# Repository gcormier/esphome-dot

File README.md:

# esphome-dot

Beginnings of a replacement PCB for Amazon Echo Dot v5.

# todo
- [x] Physical board dimensions
- [ ] Figure out pinout of ribbon cable
- [ ] figure out PDN mystery. it needs to be controlled to use register 0x00 for pullup settings
- [ ] Determine if ESP32 module can be used or needs custom design for RF purposes
- [ ] Schematic
- [ ] PCB design and layout
- [ ] BOM
- [ ] Firmware
- [ ] Manufacture

## dfm
- [ ] Holes around spring fingers for protective cap (1.6mm hole, 1.5mm plastic pin)

## Notice
Amazon Echo Dot is a trademark of Amazon.com, Inc. This project is not affiliated with Amazon.com, Inc. in any way.

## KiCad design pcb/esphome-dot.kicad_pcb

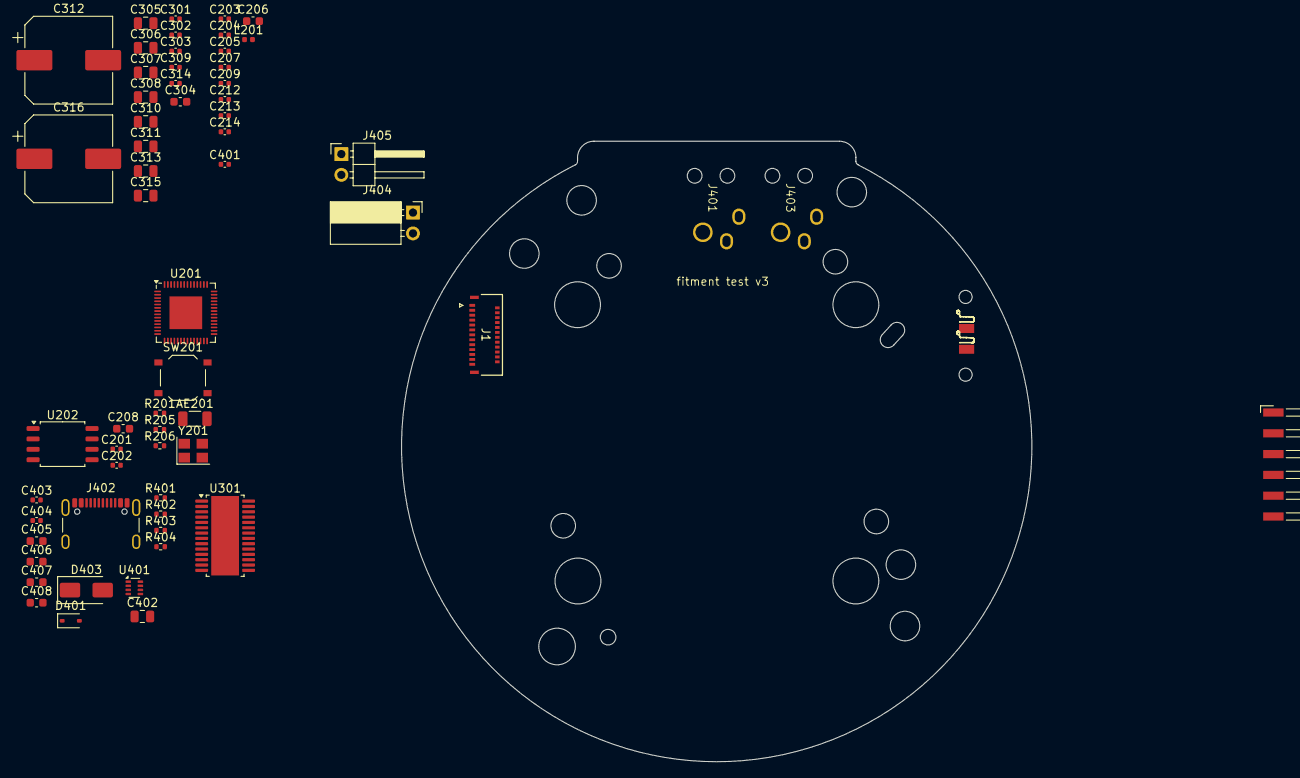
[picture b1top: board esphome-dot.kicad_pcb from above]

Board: 4 copper layers, 77.0 x 75.8 mm, 62 parts (0 on the bottom side), 44 nets, no tracks yet.

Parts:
AE201: ANT3216LL00R2400A; C_1206_3216Metric
C201, C202: 20pF; C_0402_1005Metric
C203, C205, C207, C209, C212, C213, C214, C303, C309, C314, C401, C403, C404: 100n; C_0402_1005Metric
C204, C301, C302: 1u; C_0402_1005Metric
C206, C208, C304, C405, C407, C408: 10u; C_0603_1608Metric
C305, C306, C307, C308: 220n; C_0805_2012Metric
C310, C315: 22u; C_0805_2012Metric
C311, C313: 680n; C_0805_2012Metric
C312, C316: 330u; CP_Elec_10x10.5
C402: 10u; C_0805_2012Metric
C406: 27p; C_0603_1608Metric
D401: CUS05S40.H3F; D_SOD-323
D403: SMAJ22A; D_SMA
J1: Input; CONN_502598-2593_MOLEX
J5: SPK1; SF2212
J6: SPK2; SF2212
J201: eflashy32; Harwin_M20-89006xx_1x06_P2.54mm_Horizontal
J401, J403: ADC-055B-9; BarrelJack_AdamTech_ADC-055B-9
J402: USBC; USB_C_Receptacle_GCT_USB4105-xx-A_16P_TopMnt_Horizontal
J404: 20V; PinSocket_1x02_P2.54mm_Horizontal
J405: 20v; PinHeader_1x02_P2.54mm_Horizontal
L201: 2nH; L_0402_1005Metric
R201: 22; R_0402_1005Metric
R205, R206: 10k; R_0402_1005Metric
R401, R402: 5k1; R_0402_1005Metric
R403: 68k; R_0402_1005Metric
R404: 22k; R_0402_1005Metric
SW201: RESET; SW_Push_1P1T_XKB_TS-1187A
U201: ESP32-S3R8; QFN-56-1EP_7x7mm_P0.4mm_EP4x4mm
U202: W25Q128JVSIQ; SOIC-8_5.23x5.23mm_P1.27mm
U301: TAS5805M; TSSOP-28-1EP_4.4x9.7mm_P0.65mm_EP3.4x9.7mm_Mask3.1x4.05mm
U401: TPS62932; SOT-583-8
Y201: 40MHz; Crystal_SMD_3225-4Pin_3.2x2.5mm

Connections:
3V3: C203.2, C204.2, C205.2, C206.2, C212.2, C213.2, C214.2, L201.1, U201.20 (VDD3P3_RTC), U201.46 (VDD3P3_CPU), U201.55 (VDDA), U201.56 (VDDA)
3V3_RF: C209.2, L201.2, U201.2 (VDD3P3), U201.3 (VDD3P3)
+3V3: C303.1, C304.1, C405.1, C406.1, C407.1, C408.1, J201.4, R205.1, R206.1, R403.2, U301.2 (DVDD)
+20V: C309.2, C310.2, C312.2, C314.2, C315.2, C316.2, C402.1, C403.2, D401.1 (K), D403.1 (K), J403.1, J405.1, U301.15 (PVDD), U301.16 (PVDD), U301.27 (PVDD), U301.28 (PVDD), U401.3 (VIN)
/MCU/EN: C208.2, J201.5, R205.2, U201.4 (CHIP_PU)
/MCU/GPIO0: J201.6, R206.2, SW201.1 (A), U201.5 (GPIO0)
/MCU/PROGRXD: J201.3, U201.50 (U0RXD)
/MCU/PROGTXD: J201.2, U201.49 (U0TXD)
/MCU/XTAL_N: C202.2, U201.53 (XTAL_N), Y201.3
/MCU/XTAL_P: R201.1, U201.54 (XTAL_P)
/Power/BST: C404.2, U401.6 (BST)
/Power/FB: C406.2, R403.1, R404.1, U401.8 (FB)
/Power/SW: C404.1, U401.5 (SW)
ADR: U201.41 (GPIO36), U301.3 (ADR)
GND: C201.1, C202.1, C203.1, C204.1, C205.1, C206.1, C207.2, C208.1, C209.1, C212.1, C213.1, C214.1, C301.1, C302.1, C303.2, C304.2, C309.1, C310.1, C311.1, C312.1, C313.1, C314.1, C315.1, C316.1, C401.1, C402.2, C403.1, C405.2, C407.2, C408.2, D403.2 (A), J201.1, J401.2, J402.A1 (GND), J402.A12 (GND), J402.B1 (GND), J402.B12 (GND), J403.2, J404.2, J405.2, R401.2, R402.2, R404.2, SW201.2 (B), U201.57 (GND), U202.4 (GND), U301.1 (DGND), U301.5 (DGND), U301.14 (AGND), U301.19 (PGND), U301.24 (PGND), U301.29 (EP), U401.1 (RT), U401.4 (GND), Y201.2, Y201.4
I2C_SDA: U201.18 (GPIO13), U301.10 (SDA)
I2C_SDL: U201.17 (GPIO12), U301.11 (SCL)
I2S1_CLK: U201.10 (GPIO5), U301.7 (SCLK)
I2S1_FSYNC: U201.9 (GPIO4), U301.6 (LRCLK)
I2S1_SD: U201.11 (GPIO6), U301.8 (SDIN)
unnamed: C201.2, R201.2, Y201.1
unnamed: D401.2 (A), J402.A4 (VBUS), J402.A9 (VBUS), J402.B4 (VBUS), J402.B9 (VBUS)
unnamed: J402.A5 (CC1), R402.1
unnamed: J402.B5 (CC2), R401.1
unnamed: J401.1, J404.1
unnamed: C302.2, U301.13 (AVDD)
unnamed: C305.1, U301.25 (BST_A+)
unnamed: C308.1, U301.22 (BST_A-)
unnamed: C306.1, U301.18 (BST_B+)
unnamed: C307.1, U301.21 (BST_B-)
unnamed: C305.2, C308.2, U301.23 (OUT_A-), U301.26 (OUT_A+)
unnamed: C306.2, C307.2, U301.17 (OUT_B+), U301.20 (OUT_B-)
unnamed: C301.2, U301.4 (VR_DIG)
unnamed: C401.2, U401.7 (SS)
PDN: U201.40 (GPIO35), U301.12 (~PDN)
SPI_CLK: U201.33 (SPICLK), U202.6 (CLK)
SPI_CS0: U201.32 (SPICS0), U202.1 (~CS)
SPI_DI: U201.35 (SPID), U202.5 (DI(IO0))
SPI_DO: U201.34 (SPIQ), U202.2 (DO(IO1))
SPI_HD: U201.30 (SPIHD), U202.7 (IO3)
SPI_WP: U201.31 (SPIWP), U202.3 (IO2)
USB+: J402.A6 (D+), J402.B6 (D+), U201.26 (GPIO20/USB_D+)
USB-: J402.A7 (D-), J402.B7 (D-), U201.25 (GPIO19/USB_D-)
VDD_SPI: C207.1, U201.29 (VDD_SPI), U202.8 (VCC)

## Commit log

2024-06-08 initial
2024-06-08 test pcb
2024-06-14 readme
2024-07-11 pcb-fitment-v2
2024-07-16 3d model
2024-07-22 fix footprint
2024-07-22 schematic and tweaks
2024-10-31 notes
2024-10-31 moar
2024-11-02 updates yo
2024-11-02 tiny
2024-11-02 i2c works
